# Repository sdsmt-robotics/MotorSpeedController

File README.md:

# MotorSpeedController  
yaya.

# Hardware  

# Software  
Contains code for the controller itself and code for a master device to interface with the controller.  
 * **controller** - Code for the speed controller itself.  
 * **controllerInterfaceLib** - Library files for use on a master device to interface with the controller.  
 
  ## Wiring Connections and Interface  
 This controller uses standard SPI communications.  
| Arduino | Speed Controller |
|---------|------------------|
| 5V      | 5V               |
| GND     | GND              |
| MOSI    | MOSI             |
| MISO    | MISO             |
| SCK     | SCK              |
| SS*     | SS               |  

*The SS pin must be used for *at least one* of the connections. Additional speed controllers may use other digital IO pins.  
  
## Status LED  
The green LED on the board will indicate state of the controller. The key is as follows.
| State         | Pattern    |
|---------------|------------|
| Off           | ---------  |
| Brake         | -\_\_-\_\_-\_\_  |
| Speed Control | --\_\_--\_\_-- |
| Power Control | --\_--\_--\_  |
| Timeout       | -\_-\_-\_-\_-  |  
 
## Interface Lib Usage  
**Create:**  
Create an instance of the class.  

    Nidec24hController motor(SPI, ssPin);  

*SPI* - the SPI singleton object from the SPI.h library.  
*ssPin* - pin to use as chip select. Should simply be SS for first controller.  

**Initialize:**  
Create an instance of the class.  

    setup() {
        ...
        // Init SPI
        SPI.begin ();
        SPI.setClockDivider(SPI_CLOCK_DIV4);
        
        //Init motor controller
        motor.init();  
        ...
    }

**Set Speed:**  
Set the speed for the motor in RPM. Negative values are allowed. This will switch the motor to speed control mode if in power control mode or braking.  

    motor.setSpeed(speed);  

*speed* - the speed for the motor in RPM.  

**Set Power:**  
Set the power for the motor (-1000 to 1000). This will switch the motor to power control mode if in speed control mode or braking.  

    motor.setPower(power);  

*power* - the power for the motor (-1000 to 1000).  

**Brake:**  
Engage the electronic braking and stop the motor..  

    motor.brake();  

**Set Direction Inverted:**  
Set whether the motor control should be inverted.  

    motor.invertDirection(invertDir);  

*invertDir* - boolean to set if direction should be inverted.  

**Get Current Speed:**  
Get the current speed of the motor in RPM.   

    motor.getSpeed();  

**Get Current Power:**  
Get the current power the motor is running at. If in speed control mode, this will be varied automatically by the PID algorithm.  

    motor.getPower();  

**Get the Target Speed:**  
Get the target speed the controller is attempting to regulate the motor at.  

    motor.getTargetSpeed();

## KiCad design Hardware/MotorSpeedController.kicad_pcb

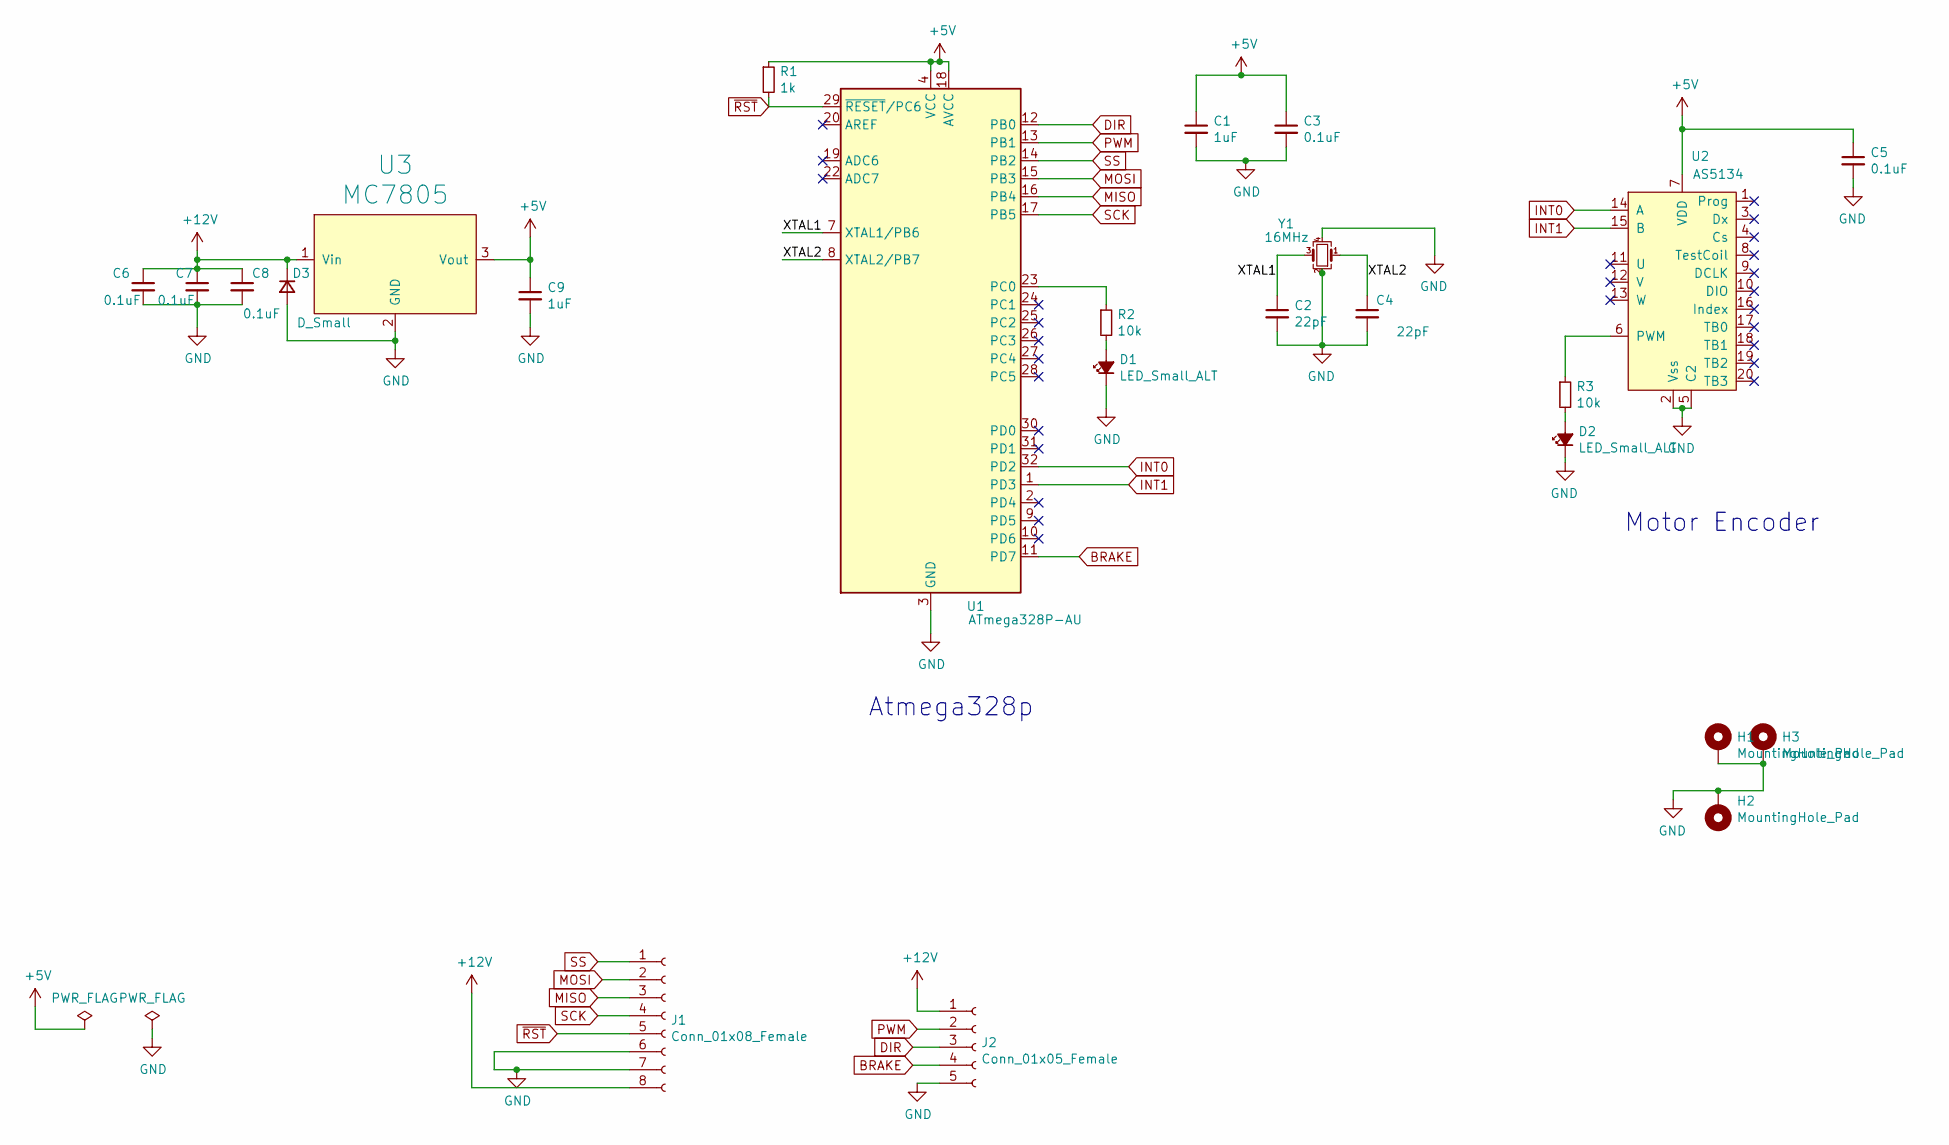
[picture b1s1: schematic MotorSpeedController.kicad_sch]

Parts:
C1, C9: 1uF; C_0603_1608Metric; Digikey 587-6280-1-ND‎
C2, C4: 22pF; C_0603_1608Metric; Digikey 478-0603YA220KAT2ACT-ND‎
C3, C5, C6, C7, C8: 0.1uF; C_0603_1608Metric; Digikey 1276-1941-1-ND
D1: LED_Small_ALT; D_0603_1608Metric_Castellated; Digikey 160-1183-1-ND
D2: LED_Small_ALT; D_0603_1608Metric_Castellated; Digikey 160-1182-1-ND‎
D3: D_Small; D_2010_5025Metric_Castellated; Digikey 478-7812-1-ND
H1, H2, H3: MountingHole_Pad; MountingHole_3mm_Pad_Via
J1: Conn_01x08_Female; PinHeader_1x08_P2.54mm_Vertical
J2: Conn_01x05_Female; PinHeader_1x05_P2.54mm_Vertical
R1: 1k; R_0603_1608Metric; Digikey P124100CT-ND‎
R2, R3: 10k; R_0603_1608Metric; Digikey P124100CT-ND‎
U1: ATmega328P-AU; TQFP-32_7x7mm_P0.8mm
U2: AS5134; SOIC-20; Digikey AS5134-ZSSMCT-ND‎
U3: MC7805; TO-252-2; Digikey MC7805CDTRKGOSCT-ND
Y1: 16MHz; Crystal_SMD_3225-4Pin_3.2x2.5mm; Digikey 2151-RH100-16.000-12-1010-EXT-TRCT-ND

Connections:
+5V: C1.1, C3.1, C5.1, C9.1, R1.1, U1.4 (VCC), U1.6 (VCC), U1.18 (AVCC), U2.7 (VDD), U3.3 (Vout)
+12V: C6.1, C7.1, C8.1, D3.1 (K), J1.8, J2.1, U3.1 (Vin)
/XTAL1: C2.1, U1.7 (XTAL1/PB6), Y1.3
/XTAL2: C4.1, U1.8 (XTAL2/PB7), Y1.1
BRAKE: J2.4, U1.11 (PD7)
DIR: J2.3, U1.12 (PB0)
GND: C1.2, C2.2, C3.2, C4.2, C5.2, C6.2, C7.2, C8.2, C9.2, D1.1 (K), D2.1 (K), D3.2 (A), H1.1, H2.1, H3.1, J1.6, J1.7, J2.5, U1.3 (GND), U1.5 (GND), U1.21 (GND), U2.2 (Vss), U2.5 (C2), U3.2 (GND), Y1.2, Y1.4
INT0: U1.32 (PD2), U2.14 (A)
INT1: U1.1 (PD3), U2.15 (B)
MISO: J1.3, U1.16 (PB4)
MOSI: J1.2, U1.15 (PB3)
unnamed: D1.2 (A), R2.2
unnamed: D2.2 (A), R3.2
unnamed: R2.1, U1.23 (PC0)
unnamed: R3.1, U2.6 (PWM)
PWM: J2.2, U1.13 (PB1)
SCK: J1.4, U1.17 (PB5)
SS: J1.1, U1.14 (PB2)
~RST: J1.5, R1.2, U1.29 (~RESET/PC6)

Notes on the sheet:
Motor Encoder
Atmega328p

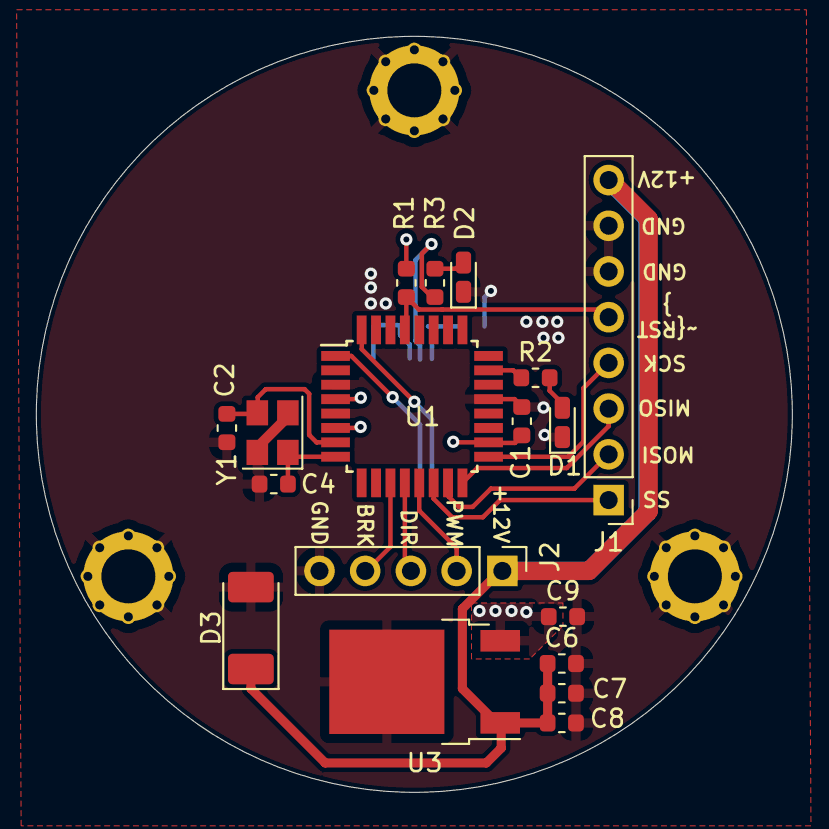
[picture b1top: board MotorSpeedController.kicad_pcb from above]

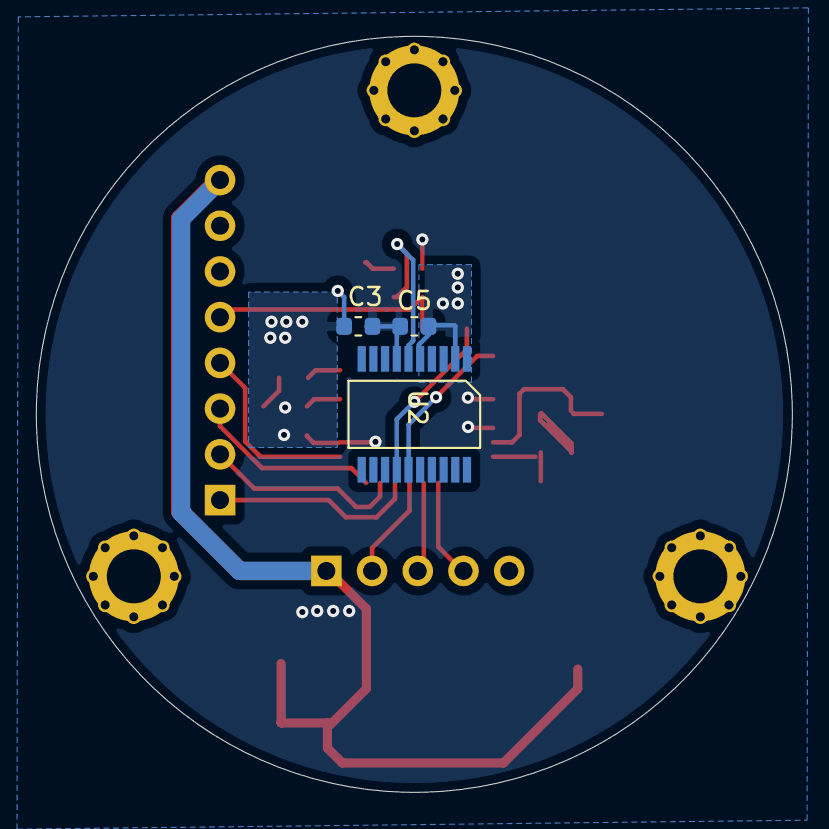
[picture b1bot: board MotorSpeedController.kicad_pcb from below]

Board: 2 copper layers, 42.0 x 42.0 mm, 24 parts (3 on the bottom side), 19 nets.

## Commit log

2021-01-09 Initial versions of files pulled from other projects
2021-01-17 Deleted Dupilicate file
2021-01-18 Working controller and interface code
    - Code for the controller is working as far as I can tell and so is the interface code.
    - PID values need adjusting.
    - Code could use some more testing.
    - Significant cleanup needed (sorry).
2021-01-18 Move some things around
2021-01-18 Added pull downs in Interrupt pins
2021-01-19 Addded gitignore
2021-01-19 Added a discrete PID library
2021-01-20 Implement the new PID library
2021-01-23 Updated Footprints for better fit
2021-01-24 Changed PCB Dimensions. Added +5V regulator. Made headers bigger
2021-01-24 Prevent soldermask from Bottom +12V rail so we can solder wire to it
2021-01-27 Improved filter. Tuned PID
2021-01-30 Added Final CAM files and updated BOM
2021-02-27 removed reference to unused library
2021-03-19 Improve SPI communication reliability on interface lib
2021-03-23 Further improve SPI reliability
2021-03-23 Clean up code and split out testing functions
2021-03-23 Add changes to oscilating speed example
2021-03-23 Added comments and cleaned up the code.
2021-03-27 Modified the filter class to use doubles instead of ints.
2021-03-30 Add timer to prevent sending commands too quickly
2021-03-30 Adjust PID tuning and add blinking lights
2021-04-01 Improve SPI and add communication timeout
2022-03-04 Updated to KiCAD 6
2022-03-04 Forgot to update zip file to KiCAD 6
